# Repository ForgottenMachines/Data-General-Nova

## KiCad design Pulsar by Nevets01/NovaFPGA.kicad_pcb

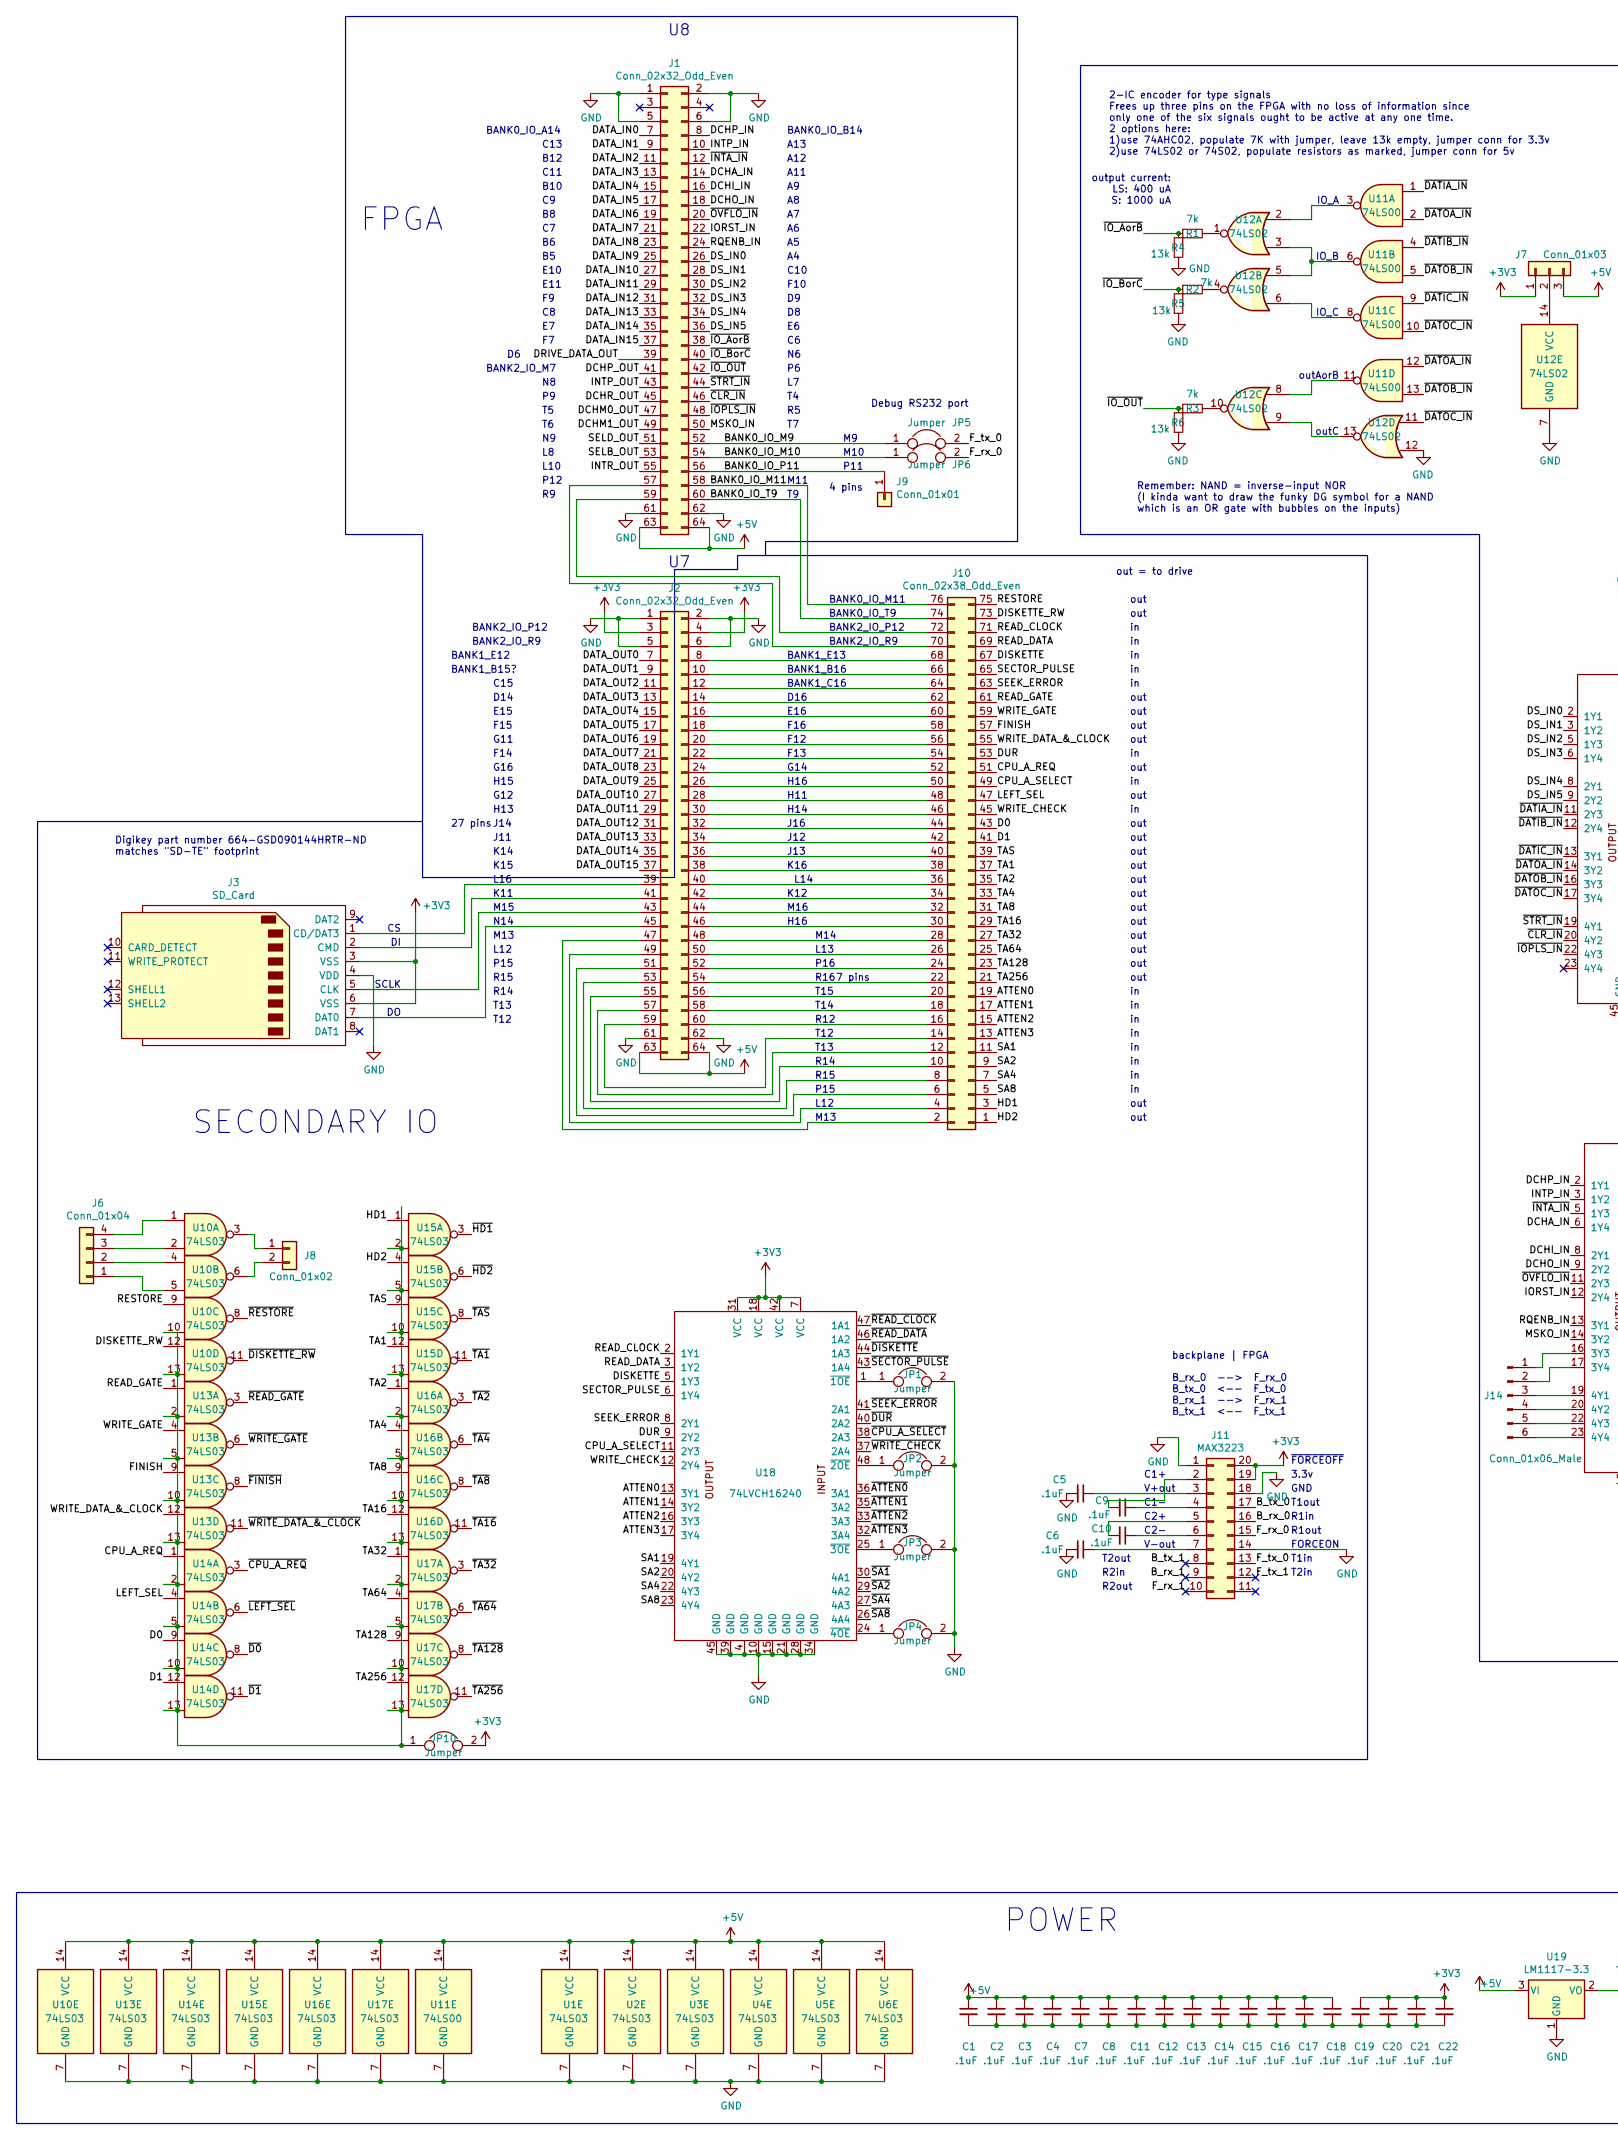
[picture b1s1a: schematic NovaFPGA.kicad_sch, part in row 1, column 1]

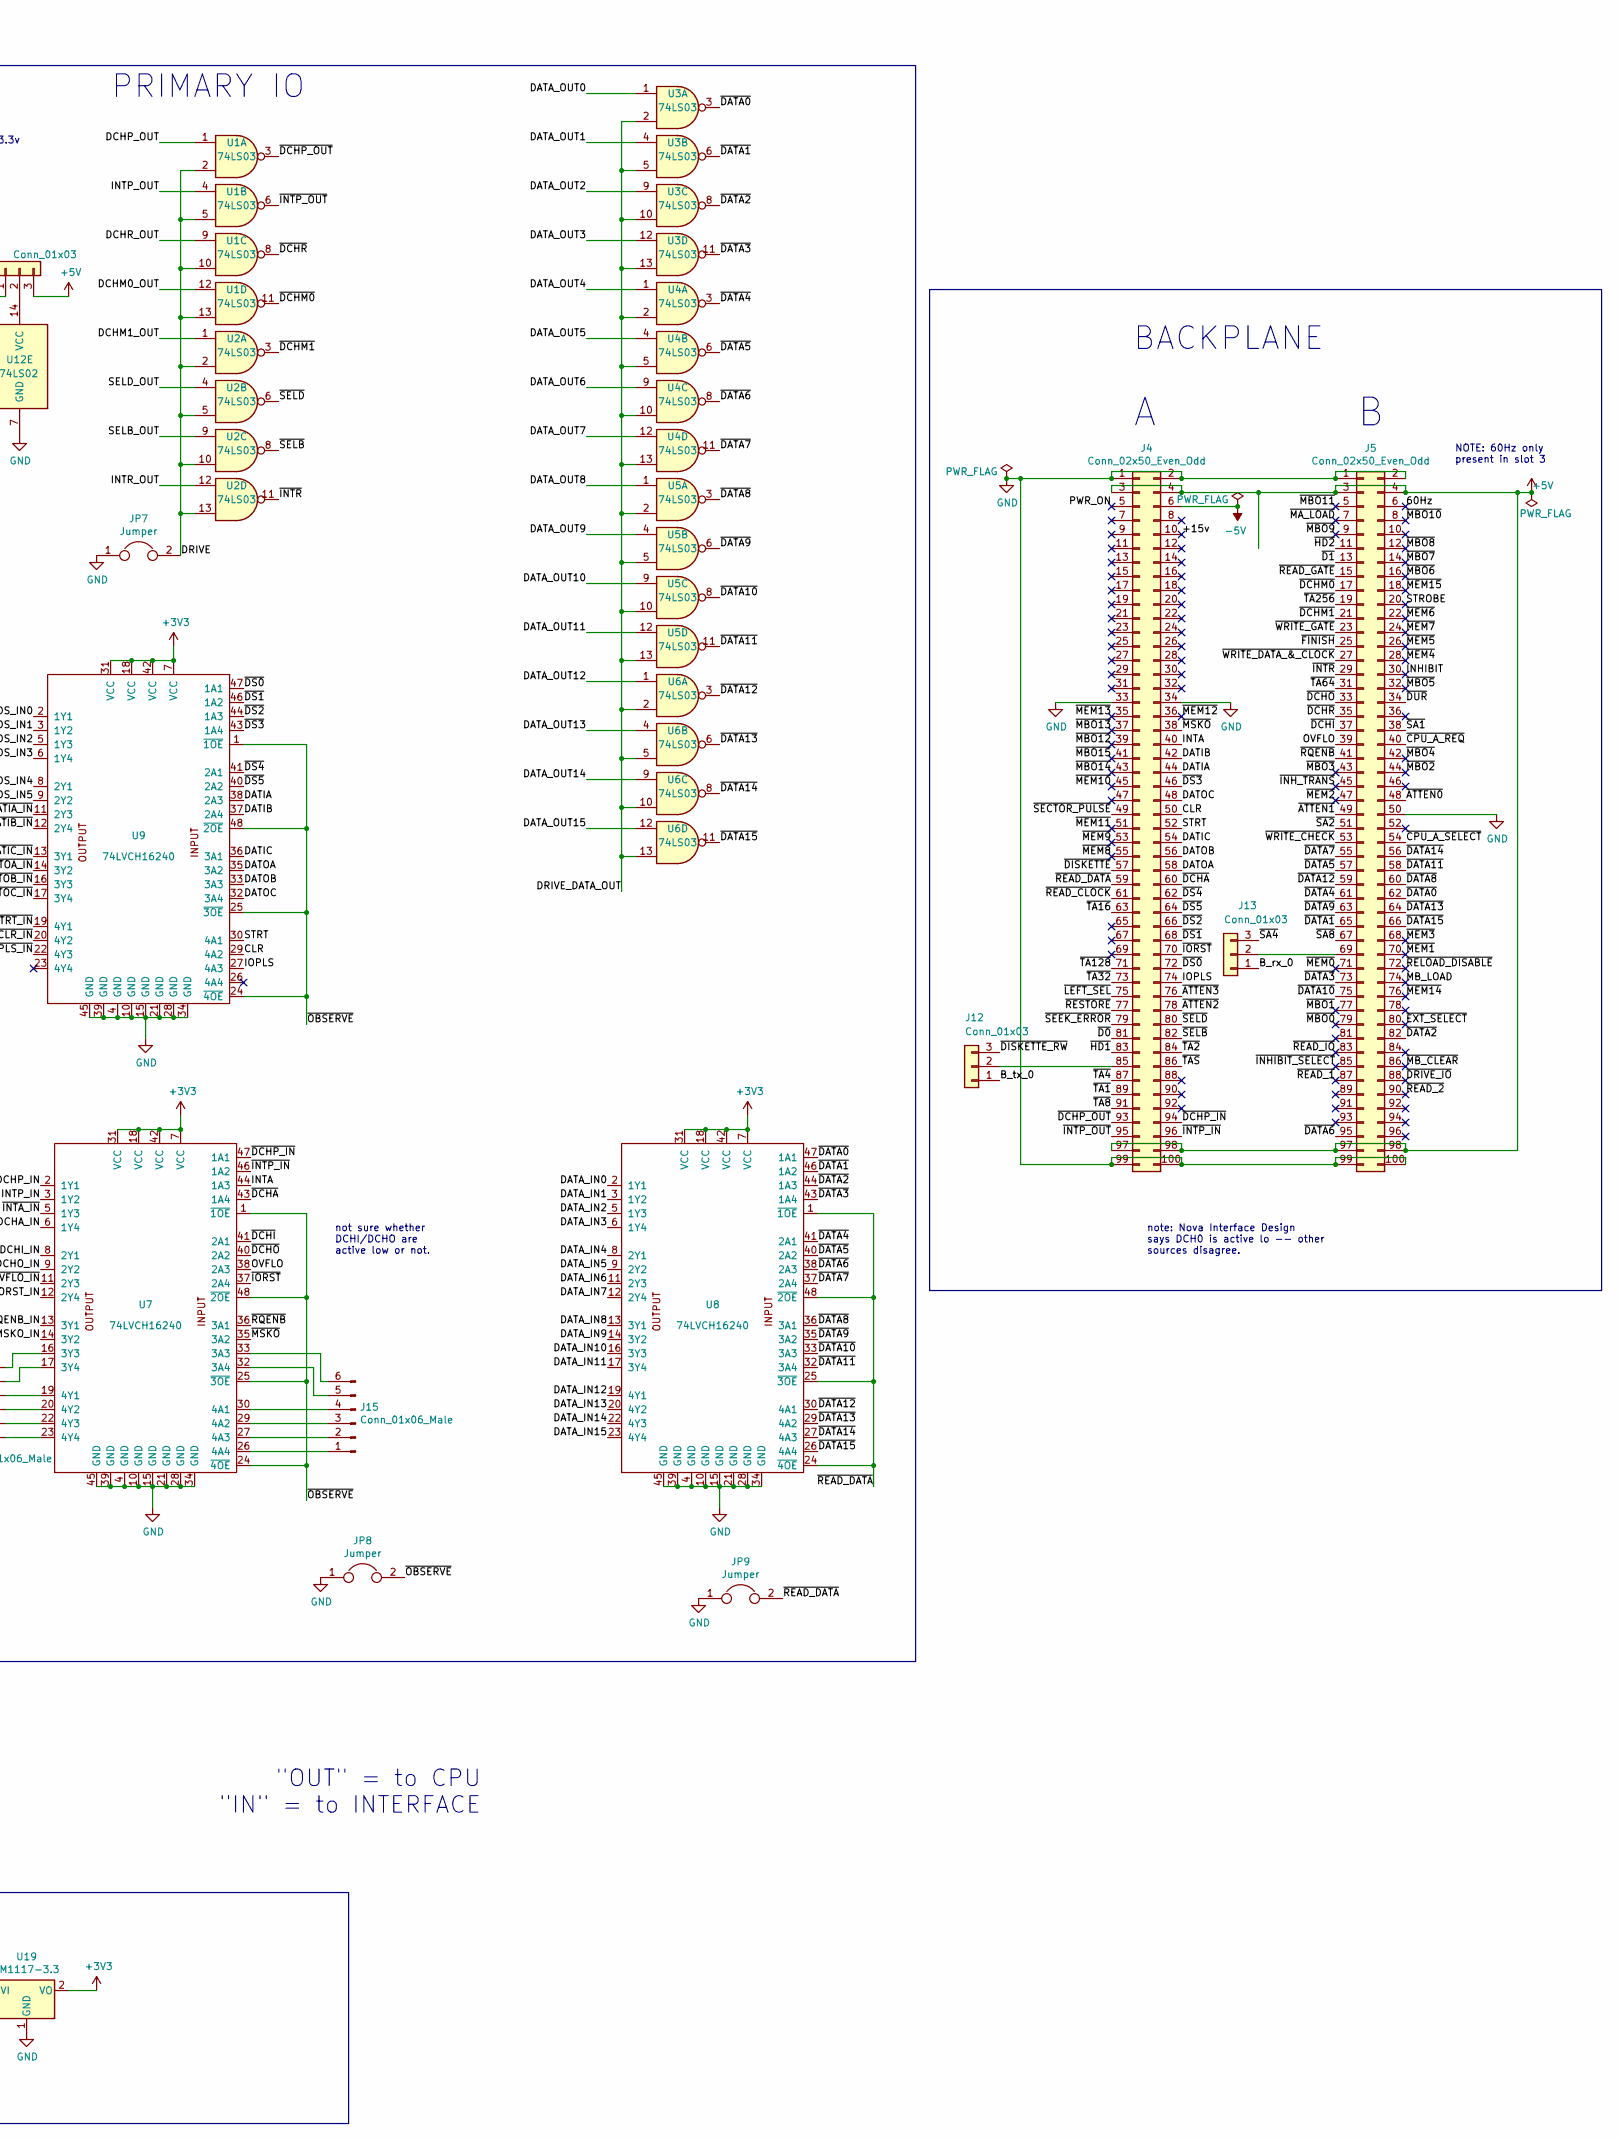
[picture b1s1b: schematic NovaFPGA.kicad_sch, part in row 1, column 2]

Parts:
C1, C2, C3, C4, C5, C6, C7, C8, C9, C10, C11, C12, C13, C14, C15, C16, C17, C18, C19, C20, C21, C22: .1uF; C_Disc_D3.4mm_W2.1mm_P2.50mm
J1, J2: Conn_02x32_Odd_Even; PinHeader_2x32_P2.54mm_Vertical
J3: SD_Card; SD_TE_2041021
J4: Conn_02x50_Even_Odd; portA_NovaMod
J5: Conn_02x50_Even_Odd; portB_NovaMod
J6: Conn_01x04; PinHeader_1x04_P2.54mm_Vertical
J7, J12, J13: Conn_01x03; PinHeader_1x03_P2.54mm_Vertical
J8: Conn_01x02; PinHeader_1x02_P2.54mm_Vertical
J9: Conn_01x01; PinHeader_1x01_P2.54mm_Vertical
J10: Conn_02x38_Odd_Even; PinHeader_2x38_P2.54mm_Vertical
J11: MAX3223; DIP-20_W7.62mm_Socket_LongPads
J14, J15: Conn_01x06_Male; PinHeader_1x06_P2.54mm_Vertical
JP1, JP2, JP3, JP4, JP5, JP6, JP7, JP8, JP9, JP10: Jumper; PinHeader_1x02_P2.54mm_Vertical
R1, R2, R3: 7k; R_Axial_DIN0309_L9.0mm_D3.2mm_P15.24mm_Horizontal
R4, R5, R6: 13k; R_Axial_DIN0309_L9.0mm_D3.2mm_P15.24mm_Horizontal
U1, U2, U3, U4, U5, U6, U10, U13, U14, U15, U16, U17: 74LS03; DIP-14_W7.62mm_Socket_LongPads
U7, U8, U9, U18: 74LVCH16240; SSOP-48_7.5x15.9mm_P0.635mm
U11: 74LS00; DIP-14_W7.62mm_Socket_LongPads
U12: 74LS02; DIP-14_W7.62mm_Socket_LongPads
U19: LM1117-3.3; TO-220-3_Horizontal_TabDown

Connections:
-5V: J4.6
/60Hz: J5.6
/+15v: J4.10
/ATTEN0: J10.19, U18.13 (3Y1)
/ATTEN1: J10.17, U18.14 (3Y2)
/ATTEN2: J10.15, U18.16 (3Y3)
/ATTEN3: J10.13, U18.17 (3Y4)
/BANK0_IO_M9: J1.52, JP5.1
/BANK0_IO_M10: J1.54, JP6.1
/BANK0_IO_M11: J1.58, J10.76
/BANK0_IO_P11: J1.56, J9.1
/BANK0_IO_T9: J1.60, J10.74
/B_rx_0: J11.16, J13.1
/B_rx_1: J11.9
/B_tx_0: J11.17, J12.1
/B_tx_1: J11.8
/CLR: J4.50, U9.29 (4A2)
/CPU_A_REQ: J10.51, U14.1
/CPU_A_SELECT: J10.49, U18.11 (2Y3)
/D0: J10.43, U14.9
/D1: J10.41, U14.12
/DATA_IN0: J1.7, U8.2 (1Y1)
/DATA_IN1: J1.9, U8.3 (1Y2)
/DATA_IN2: J1.11, U8.5 (1Y3)
/DATA_IN3: J1.13, U8.6 (1Y4)
/DATA_IN4: J1.15, U8.8 (2Y1)
/DATA_IN5: J1.17, U8.9 (2Y2)
/DATA_IN6: J1.19, U8.11 (2Y3)
/DATA_IN7: J1.21, U8.12 (2Y4)
/DATA_IN8: J1.23, U8.13 (3Y1)
/DATA_IN9: J1.25, U8.14 (3Y2)
/DATA_IN10: J1.27, U8.16 (3Y3)
/DATA_IN11: J1.29, U8.17 (3Y4)
/DATA_IN12: J1.31, U8.19 (4Y1)
/DATA_IN13: J1.33, U8.20 (4Y2)
/DATA_IN14: J1.35, U8.22 (4Y3)
/DATA_IN15: J1.37, U8.23 (4Y4)
/DATA_OUT0: J2.7, U3.1
/DATA_OUT1: J2.9, U3.4
/DATA_OUT2: J2.11, U3.9
/DATA_OUT3: J2.13, U3.12
/DATA_OUT4: J2.15, U4.1
/DATA_OUT5: J2.17, U4.4
/DATA_OUT6: J2.19, U4.9
/DATA_OUT7: J2.21, U4.12
/DATA_OUT8: J2.23, U5.1
/DATA_OUT9: J2.25, U5.4
/DATA_OUT10: J2.27, U5.9
/DATA_OUT11: J2.29, U5.12
/DATA_OUT12: J2.31, U6.1
/DATA_OUT13: J2.33, U6.4
/DATA_OUT14: J2.35, U6.9
/DATA_OUT15: J2.37, U6.12
/DATIA: J4.44, U9.38 (2A3)
/DATIB: J4.42, U9.37 (2A4)
/DATIC: J4.54, U9.36 (3A1)
/DATOA: J4.58, U9.35 (3A2)
/DATOB: J4.56, U9.33 (3A3)
/DATOC: J4.48, U9.32 (3A4)
/DCHA_IN: J1.14, U7.6 (1Y4)
/DCHI_IN: J1.16, U7.8 (2Y1)
/DCHM0_OUT: J1.47, U1.12
/DCHM1_OUT: J1.49, U2.1
/DCHO_IN: J1.18, U7.9 (2Y2)
/DCHP_IN: J1.8, U7.2 (1Y1)
/DCHP_OUT: J1.41, U1.1
/DCHR_OUT: J1.45, U1.9
/DISKETTE: J10.67, U18.5 (1Y3)
/DISKETTE_RW: J10.73, U10.12
/DRIVE: JP7.2, U1.2, U1.5, U1.10, U1.13, U2.2, U2.5, U2.10, U2.13
/DRIVE_DATA_OUT: J1.39, U3.2, U3.5, U3.10, U3.13, U4.2, U4.5, U4.10, U4.13, U5.2, U5.5, U5.10, U5.13, U6.2, U6.5, U6.10, U6.13
/DS_IN0: J1.26, U9.2 (1Y1)
/DS_IN1: J1.28, U9.3 (1Y2)
/DS_IN2: J1.30, U9.5 (1Y3)
/DS_IN3: J1.32, U9.6 (1Y4)
/DS_IN4: J1.34, U9.8 (2Y1)
/DS_IN5: J1.36, U9.9 (2Y2)
/DUR: J10.53, U18.9 (2Y2)
/FINISH: J10.57, U13.9
/F_rx_0: J11.15, JP6.2
/F_rx_1: J11.10
/F_tx_0: J11.13, JP5.2
/F_tx_1: J11.12
/HD1: J10.3, U15.1
/HD2: J10.1, U15.4
/INHIBIT: J5.30
/INTA: J4.40, U7.44 (1A3)
/INTP_IN: J1.10, U7.3 (1Y2)
/INTP_OUT: J1.43, U1.4
/INTR_OUT: J1.55, U2.12
/IOPLS: J4.74, U9.27 (4A3)
/IORST_IN: J1.22, U7.12 (2Y4)
/LEFT_SEL: J10.47, U14.4
/MB_LOAD: J5.74
/MSKO_IN: J1.50, U7.14 (3Y2)
/OVFLO: J5.39, U7.38 (2A3)
/PWR_ON: J4.5
/READ_CLOCK: J10.71, U18.2 (1Y1)
/READ_DATA: J10.69, U18.3 (1Y2)
/READ_GATE: J10.61, U13.1
/RESTORE: J10.75, U10.9
/RQENB_IN: J1.24, U7.13 (3Y1)
/SA1: J10.11, U18.19 (4Y1)
/SA2: J10.9, U18.20 (4Y2)
/SA4: J10.7, U18.22 (4Y3)
/SA8: J10.5, U18.23 (4Y4)
/SECTOR_PULSE: J10.65, U18.6 (1Y4)
/SEEK_ERROR: J10.63, U18.8 (2Y1)
/SELB_OUT: J1.53, U2.9
/SELD_OUT: J1.51, U2.4
/STROBE: J5.20
/STRT: J4.52, U9.30 (4A1)
/TA1: J10.37, U15.12
/TA2: J10.35, U16.1
/TA4: J10.33, U16.4
/TA8: J10.31, U16.9
/TA16: J10.29, U16.12
/TA32: J10.27, U17.1
/TA64: J10.25, U17.4
/TA128: J10.23, U17.9
/TA256: J10.21, U17.12
/TAS: J10.39, U15.9
/WRITE_CHECK: J10.45, U18.12 (2Y4)
/WRITE_DATA_&_CLOCK: J10.55, U13.12
/WRITE_GATE: J10.59, U13.4
/~ATTEN0: J5.48, U18.36 (3A1)
/~ATTEN1: J5.49, U18.35 (3A2)
/~ATTEN2: J4.78, U18.33 (3A3)
/~ATTEN3: J4.76, U18.32 (3A4)
/~CLR_IN: J1.46, U9.20 (4Y2)
/~CPU_A_REQ: J5.40, U14.3
/~CPU_A_SELECT: J5.54, U18.38 (2A3)
/~D0: J4.81, U14.8
/~D1: J5.13, U14.11
/~DATA0: J5.62, U3.3, U8.47 (1A1)
/~DATA1: J5.65, U3.6, U8.46 (1A2)
/~DATA2: J5.82, U3.8, U8.44 (1A3)
/~DATA3: J5.73, U3.11, U8.43 (1A4)
/~DATA4: J5.61, U4.3, U8.41 (2A1)
/~DATA5: J5.57, U4.6, U8.40 (2A2)
/~DATA6: J5.95, U4.8, U8.38 (2A3)
/~DATA7: J5.55, U4.11, U8.37 (2A4)
/~DATA8: J5.60, U5.3, U8.36 (3A1)
/~DATA9: J5.63, U5.6, U8.35 (3A2)
/~DATA10: J5.75, U5.8, U8.33 (3A3)
/~DATA11: J5.58, U5.11, U8.32 (3A4)
/~DATA12: J5.59, U6.3, U8.30 (4A1)
/~DATA13: J5.64, U6.6, U8.29 (4A2)
/~DATA14: J5.56, U6.8, U8.27 (4A3)
/~DATA15: J5.66, U6.11, U8.26 (4A4)
/~DATIA_IN: U9.11 (2Y3), U11.1
/~DATIB_IN: U9.12 (2Y4), U11.4
/~DATIC_IN: U9.13 (3Y1), U11.9
/~DATOA_IN: U9.14 (3Y2), U11.2, U11.12
/~DATOB_IN: U9.16 (3Y3), U11.5, U11.13
/~DATOC_IN: U9.17 (3Y4), U11.10, U12.11
/~DCHA: J4.60, U7.43 (1A4)
/~DCHI: J5.37, U7.41 (2A1)
/~DCHM0: J5.17, U1.11
/~DCHM1: J5.21, U2.3
/~DCHO: J5.33, U7.40 (2A2)
/~DCHP_IN: J4.94, U7.47 (1A1)
/~DCHP_OUT: J4.93, U1.3
/~DCHR: J5.35, U1.8
/~DISKETTE_RW: J12.3, U10.11
/~DISKETTE: J4.57, U18.44 (1A3)
/~DRIVE_IO: J5.88
/~DS0: J4.72, U9.47 (1A1)
/~DS1: J4.68, U9.46 (1A2)
/~DS2: J4.66, U9.44 (1A3)
/~DS3: J4.46, U9.43 (1A4)
/~DS4: J4.62, U9.41 (2A1)
/~DS5: J4.64, U9.40 (2A2)
/~DUR: J5.34, U18.40 (2A2)
/~EXT_SELECT: J5.80
/~FINISH: J5.25, U13.8
/~HD1: J4.83, U15.3
/~HD2: J5.11, U15.6
/~INHIBIT_SELECT: J5.85
/~INH_TRANS: J5.45
/~INTA_IN: J1.12, U7.5 (1Y3)
/~INTP_IN: J4.96, U7.46 (1A2)
/~INTP_OUT: J4.95, U1.6
/~INTR: J5.29, U2.11
/~IOPLS_IN: J1.48, U9.22 (4Y3)
/~IORST: J4.70, U7.37 (2A4)
/~IO_AorB: J1.38, R1.1, R4.2
/~IO_BorC: J1.40, R2.1, R5.2
/~IO_OUT: J1.42, R3.1, R6.2
/~LEFT_SEL: J4.75, U14.6
/~MA_LOAD: J5.7
/~MBO0: J5.79
/~MBO1: J5.77
/~MBO2: J5.44
/~MBO3: J5.43
/~MBO4: J5.42
/~MBO5: J5.32
/~MBO6: J5.16
/~MBO7: J5.14
/~MBO8: J5.12
/~MBO9: J5.9
/~MBO10: J5.8
/~MBO11: J5.5
/~MBO12: J4.39
/~MBO13: J4.37
/~MBO14: J4.43
/~MBO15: J4.41
/~MB_CLEAR: J5.86
/~MEM0: J5.71
/~MEM1: J5.70
/~MEM2: J5.47
/~MEM3: J5.68
/~MEM4: J5.28
/~MEM5: J5.26
/~MEM6: J5.22
/~MEM7: J5.24
/~MEM8: J4.55
/~MEM9: J4.53
/~MEM10: J4.45
/~MEM11: J4.51
/~MEM12: J4.36
/~MEM13: J4.35
/~MEM14: J5.76
/~MEM15: J5.18
/~MSKO: J4.38, U7.35 (3A2)
/~OBSERVE: JP8.2, U7.1 (~1OE), U7.24 (~4OE), U7.25 (~3OE), U7.48 (~2OE), U9.1 (~1OE), U9.24 (~4OE), U9.25 (~3OE), U9.48 (~2OE)
/~OVFLO_IN: J1.20, U7.11 (2Y3)
/~READ_1: J5.87
/~READ_2: J5.90
/~READ_CLOCK: J4.61, U18.47 (1A1)
/~READ_DATA: J4.59, JP9.2, U8.1 (~1OE), U8.24 (~4OE), U8.25 (~3OE), U8.48 (~2OE), U18.46 (1A2)
/~READ_GATE: J5.15, U13.3
/~READ_IO: J5.83
/~RELOAD_DISABLE: J5.72
/~RESTORE: J4.77, U10.8
/~RQENB: J5.41, U7.36 (3A1)
/~SA1: J5.38, U18.30 (4A1)
/~SA2: J5.51, U18.29 (4A2)
/~SA4: J13.3, U18.27 (4A3)
/~SA8: J5.67, U18.26 (4A4)
/~SECTOR_PULSE: J4.49, U18.43 (1A4)
/~SEEK_ERROR: J4.79, U18.41 (2A1)
/~SELB: J4.82, U2.8
/~SELD: J4.80, U2.6
/~STRT_IN: J1.44, U9.19 (4Y1)
/~TA1: J4.89, U15.11
/~TA2: J4.84, U16.3
/~TA4: J4.87, U16.6
/~TA8: J4.91, U16.8
/~TA16: J4.63, U16.11
/~TA32: J4.73, U17.3
/~TA64: J5.31, U17.6
/~TA128: J4.71, U17.8
/~TA256: J5.19, U17.11
/~TAS: J4.86, U15.8
/~WRITE_CHECK: J5.53, U18.37 (2A4)
/~WRITE_DATA_&_CLOCK: J5.27, U13.11
/~WRITE_GATE: J5.23, U13.6
GND: C5.2, C6.2, J1.1, J1.2, J1.5, J1.6, J1.61, J1.62, J2.1, J2.2, J2.5, J2.6, J2.61, J2.62, J3.4 (VDD), J4.1, J4.2, J4.33, J4.34, J4.99, J4.100, J5.1, J5.2, J5.50, J5.99, J5.100, J11.1, J11.14, J11.18, JP1.2, JP2.2, JP3.2, JP4.2, JP7.1, JP8.1, JP9.1, R4.1, R5.1, R6.1, U1.7 (GND), U2.7 (GND), U3.7 (GND), U4.7 (GND), U5.7 (GND), U6.7 (GND), U7.4 (GND), U7.10 (GND), U7.15 (GND), U7.21 (GND), U7.28 (GND), U7.34 (GND), U7.39 (GND), U7.45 (GND), U8.4 (GND), U8.10 (GND), U8.15 (GND), U8.21 (GND), U8.28 (GND), U8.34 (GND), U8.39 (GND), U8.45 (GND), U9.4 (GND), U9.10 (GND), U9.15 (GND), U9.21 (GND), U9.28 (GND), U9.34 (GND), U9.39 (GND), U9.45 (GND), U10.7 (GND), U11.7 (GND), U12.7 (GND), U12.12, U13.7 (GND), U14.7 (GND), U15.7 (GND), U16.7 (GND), U17.7 (GND), U18.4 (GND), U18.10 (GND), U18.15 (GND), U18.21 (GND), U18.28 (GND), U18.34 (GND), U18.39 (GND), U18.45 (GND), U19.1 (GND); also elsewhere on the board
unnamed: C1.2, C2.2, C3.2, C4.2, C7.2, C8.2, C11.2, C12.2, C13.2, C14.2, C15.2, C16.2, C17.2, C18.2, C19.2, C20.2, C21.2, C22.2
unnamed: C5.1, J11.3
unnamed: C6.1, J11.7
unnamed: C9.1, J11.4
unnamed: C9.2, J11.2
unnamed: C10.1, J11.6
unnamed: C10.2, J11.5
unnamed: J1.57, J10.70
unnamed: J1.59, J10.72
unnamed: J2.39, J3.1 (CD/DAT3)
unnamed: J2.41, J3.2 (CMD)
unnamed: J2.43, J3.5 (CLK)
unnamed: J2.45, J3.7 (DAT0)
unnamed: J6.1, U10.5
unnamed: J6.2, U10.4
unnamed: J6.3, U10.2
unnamed: J6.4, U10.1
unnamed: J7.2, U12.14 (VCC)
unnamed: J8.1, U10.3
unnamed: J8.2, U10.6
unnamed: J2.47, J10.2
unnamed: J2.49, J10.4
unnamed: J2.51, J10.6
unnamed: J2.53, J10.8
unnamed: J2.55, J10.10
unnamed: J2.57, J10.12
unnamed: J2.59, J10.14
unnamed: J2.60, J10.16
unnamed: J2.58, J10.18
unnamed: J2.56, J10.20
unnamed: J2.54, J10.22
unnamed: J2.52, J10.24
unnamed: J2.50, J10.26
unnamed: J2.48, J10.28
unnamed: J2.46, J10.30
unnamed: J2.44, J10.32
unnamed: J2.42, J10.34
unnamed: J2.40, J10.36
unnamed: J2.38, J10.38
unnamed: J2.36, J10.40
unnamed: J2.34, J10.42
unnamed: J2.32, J10.44
unnamed: J2.30, J10.46
unnamed: J2.28, J10.48
unnamed: J2.26, J10.50
unnamed: J2.24, J10.52
unnamed: J2.22, J10.54
unnamed: J2.20, J10.56
unnamed: J2.18, J10.58
unnamed: J2.16, J10.60
unnamed: J2.14, J10.62
unnamed: J2.12, J10.64
unnamed: J2.10, J10.66
unnamed: J2.8, J10.68
unnamed: J4.85, J12.2
unnamed: J5.69, J13.2
unnamed: J14.1, U7.16 (3Y3)
unnamed: J14.2, U7.17 (3Y4)
unnamed: J14.3, U7.19 (4Y1)
unnamed: J14.4, U7.20 (4Y2)
unnamed: J14.5, U7.22 (4Y3)
unnamed: J14.6, U7.23 (4Y4)
unnamed: J15.1, U7.26 (4A4)
unnamed: J15.2, U7.27 (4A3)
unnamed: J15.3, U7.29 (4A2)
unnamed: J15.4, U7.30 (4A1)
unnamed: J15.5, U7.32 (3A4)
unnamed: J15.6, U7.33 (3A3)
unnamed: JP1.1, U18.1 (~1OE)
unnamed: JP2.1, U18.48 (~2OE)
unnamed: JP3.1, U18.25 (~3OE)
unnamed: JP4.1, U18.24 (~4OE)
unnamed: JP10.1, U10.10, U10.13, U13.2, U13.5, U13.10, U13.13, U14.2, U14.5, U14.10, U14.13, U15.2, U15.5, U15.10, U15.13, U16.2, U16.5, U16.10, U16.13, U17.2, U17.5, U17.10, U17.13
unnamed: R1.2, U12.1
unnamed: R2.2, U12.4
unnamed: R3.2, U12.10
unnamed: U11.3, U12.2
unnamed: U11.6, U12.3, U12.5
unnamed: U11.8, U12.6
unnamed: U11.11, U12.8
unnamed: U12.9, U12.13

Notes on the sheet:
2-IC encoder for type signals Frees up three pins on the FPGA with no loss of information since only one of the six signals ought to be active at any one time. 2 options here: 1)use 74AHC02, populate 7K with jumper, leave 13k empty, jumper conn for 3.3v 2)use 74LS02 or 74S02, populate resistors as 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
~{FORCEOFF}
output current: LS: 400 uA S: 1000 uA
SCLK
H14
SECONDARY IO
K14
out
P15
M10
7 pins
E11
T13
IO_B
T12
B_rx_0 --> F_rx_0 B_tx_0 <-- F_tx_0 B_rx_1 --> F_rx_1 B_tx_1 <-- F_tx_1
27 pins
C15
BANK1_E13
H16
3.3v
C13
BANK2_IO_P12
FPGA
P12
BANK0_IO_T9
T1out
G12
H15
M13
T15
E16
K12
NOTE: 60Hz only present in slot 3
"OUT" = to CPU "IN" = to INTERFACE
R14
L14
J16
F15
Remember: NAND = inverse-input NOR (I kinda want to draw the funky DG symbol for a NAND which is an OR gate with bubbles on the inputs)

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
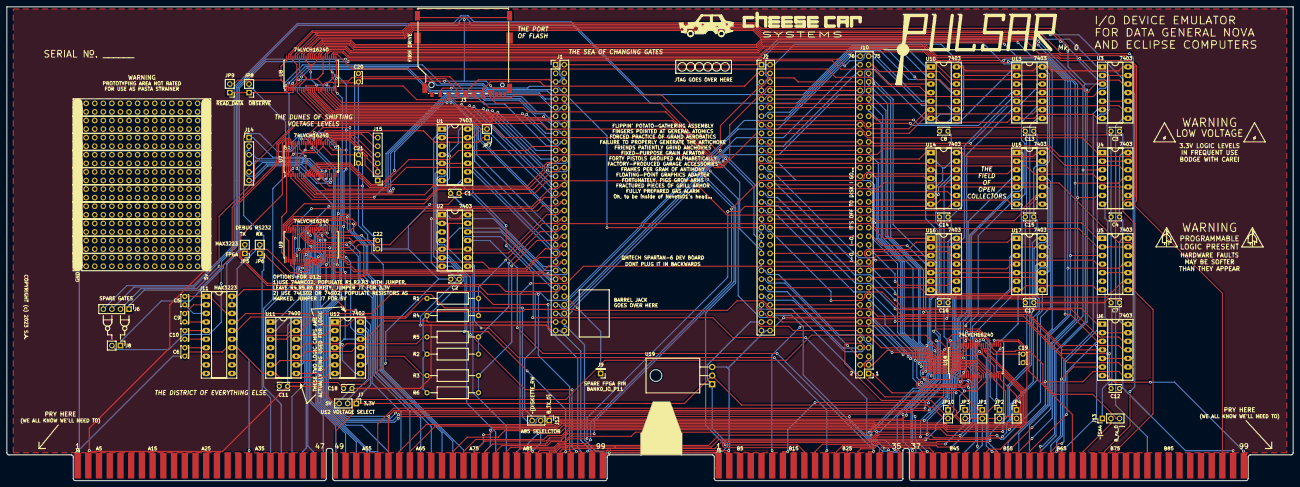
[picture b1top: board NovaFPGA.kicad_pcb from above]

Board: 2 copper layers, 381.0 x 140.3 mm, 82 parts (0 on the bottom side), 289 nets.

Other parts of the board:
 : PinHeader_2x16_P2.54mm_Vertical
 #2,  #3,  #4,  #5,  #6,  #7,  #8,  #9,  #10: PinHeader_2x16_P2.54mm_Vertical

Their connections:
GND: .1, .2, #2.1, #2.2, #3.1, #3.2, #4.1, #4.2, #5.1, #5.2, #6.1, #6.2, #7.1, #7.2, #8.1, #8.2, #9.1, #9.2, #10.1, #10.2; also elsewhere on the board

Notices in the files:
Pulsar by Nevets01/NovaFPGA.kicad_pcb:
COPYRIGHT (c) 2023 S.A.
